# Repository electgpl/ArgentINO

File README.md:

# ArgentINO
Placa de desarrollo basada en Atmega328p compatible con Arduino IDE

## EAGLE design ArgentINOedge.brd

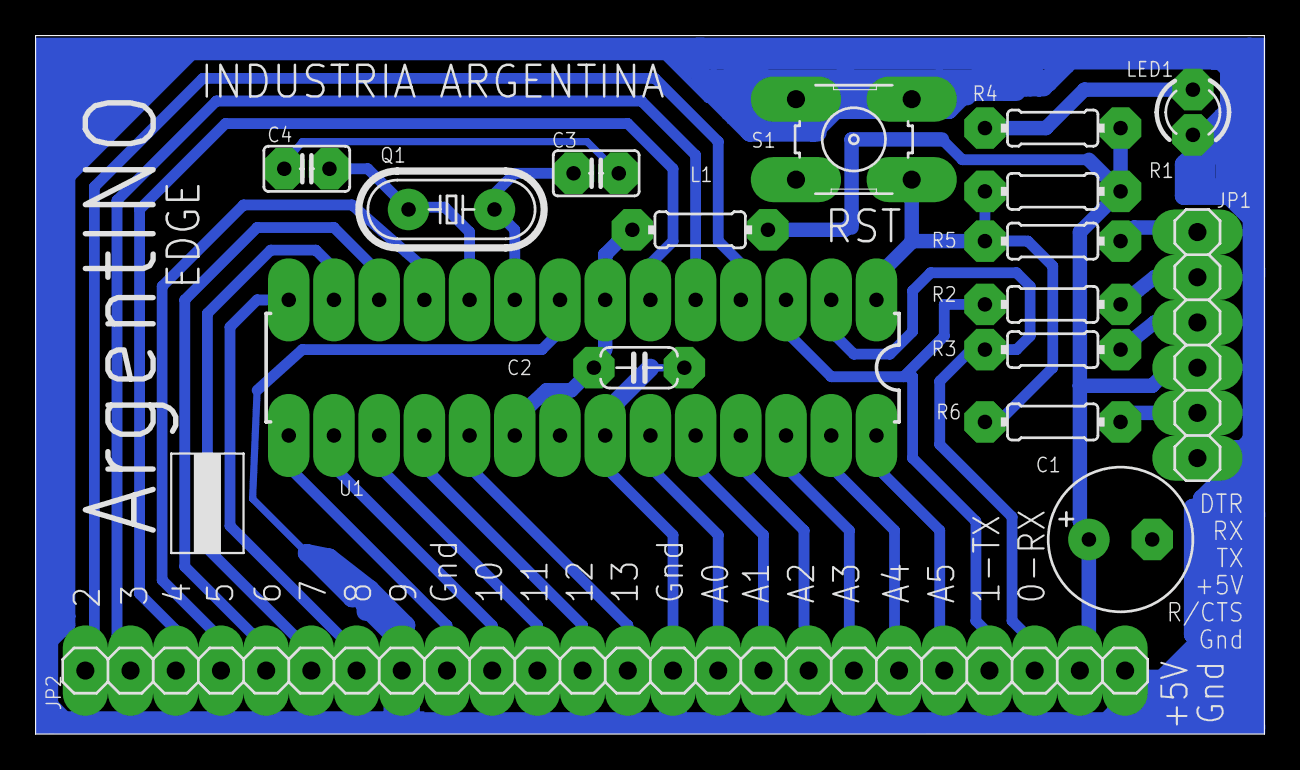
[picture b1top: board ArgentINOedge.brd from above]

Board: 2 copper layers, 69.0 x 39.2 mm, 17 parts (0 on the bottom side), 31 nets.

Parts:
C1: 470uF; E3,5-8
C2: 100nF; C050-024X044
C3, C4: 22pF; C025-025X050
JP1: 1X06
JP2: 1X24
L1: 10uHy; 0204/7
LED1: LED3MM
Q1: 16MHz; HC49/S
R1: 10k; 0204/7
R2, R3, R4: 1k; 0204/7
R5, R6: 100; 0204/7
S1: B3F-10XX
U1: ATMEGA328P_PDIP; DIL28-3

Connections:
0-RX: JP2.3, R3.2, U1.2
1-TX: JP2.4, R2.2, U1.3
2: JP2.24, U1.4
3: JP2.23, U1.5
4: JP2.22, U1.6
5: JP2.21, U1.11
6: JP2.20, U1.12
7: JP2.19, U1.13
8: JP2.18, U1.14
9: JP2.16, U1.15
10: JP2.15, U1.16
11: JP2.14, U1.17
12: JP2.13, U1.18
13: JP2.12, U1.19
+5V: C1.+, JP1.4, JP2.2, L1.1, R1.2, R4.2
A0: JP2.10, U1.23
A1: JP2.9, U1.24
A2: JP2.8, U1.25
A3: JP2.7, U1.26
A4: JP2.6, U1.27
A5: JP2.5, U1.28
DTR: JP1.1, R5.1
unnamed: C3.2, Q1.2, U1.9
unnamed: C4.2, Q1.1, U1.10
unnamed: C2.1, L1.2, U1.7, U1.20
unnamed: C1.-, C2.2, C3.1, C4.1, JP1.6, JP2.1, JP2.11, JP2.17, LED1.K, S1.3, S1.4, U1.8, U1.22
unnamed: LED1.A, R4.1
RST: R1.1, R5.2, R6.2, S1.1, U1.1
RTS: JP1.5, R6.1
RX: JP1.2, R2.1
TX: JP1.3, R3.1

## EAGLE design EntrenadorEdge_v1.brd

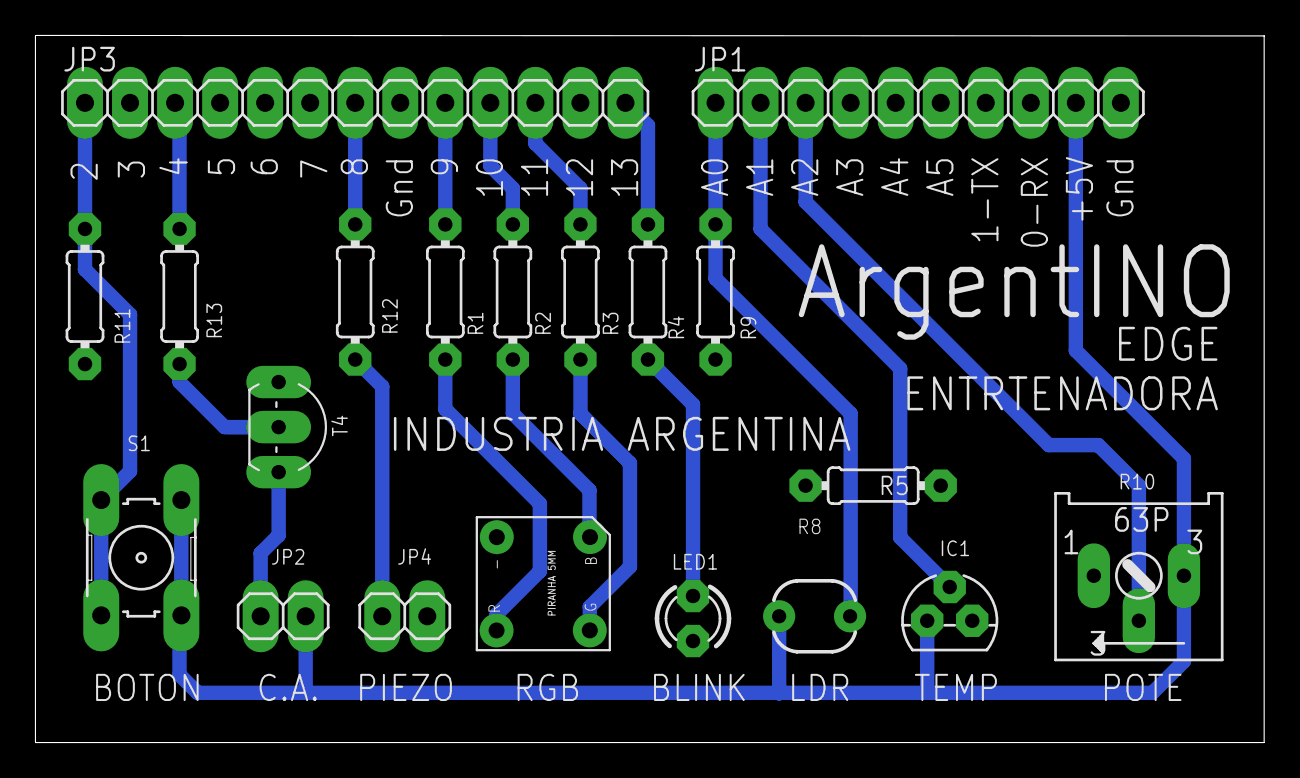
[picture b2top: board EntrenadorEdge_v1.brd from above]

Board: 2 copper layers, 69.3 x 39.9 mm, 20 parts (0 on the bottom side), 19 nets.

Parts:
IC1: LM35CZ; TO92
JP1: 1X10
JP2, JP4: 1X02
JP3: 1X13
LED1: LED3MM
R1, R2, R3: 330; 0204/7
R4, R13: 1k; 0204/7
R5: 0; 0204/7
R8: PHOTOCELLPTH; PHOTOCELL
R9, R11: 10k; 0204/7
R10: S63P
R12: 220; 0204/7
S1: B3F-10XX
T4: 2N3904; TO92-EBC
U$7: LED_PIRANHA_5MM

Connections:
2: JP3.1, R11.2, S1.1, S1.2
4: JP3.3, R13.1
8: JP3.7, R12.1
9: JP3.9, R1.1
10: JP3.10, R2.1
11: JP3.11, R3.1
13: JP3.13, R4.2
+5V: IC1.1, JP1.9, JP2.1, R8.2, R10.E, S1.3, S1.4
A0: JP1.1, R8.1, R9.2
A1: IC1.2, JP1.2
A2: JP1.3, R10.S
unnamed: R2.2, U$7.B
unnamed: R3.2, U$7.G
unnamed: R1.2, U$7.R
unnamed: JP4.2, R12.2
unnamed: R13.2, T4.B
unnamed: JP2.2, T4.C
unnamed: IC1.3, JP1.10, JP3.8, JP4.1, LED1.K, R5.1, R5.2, R9.1, R10.A, R11.1, T4.E, U$7.-
unnamed: LED1.A, R4.1

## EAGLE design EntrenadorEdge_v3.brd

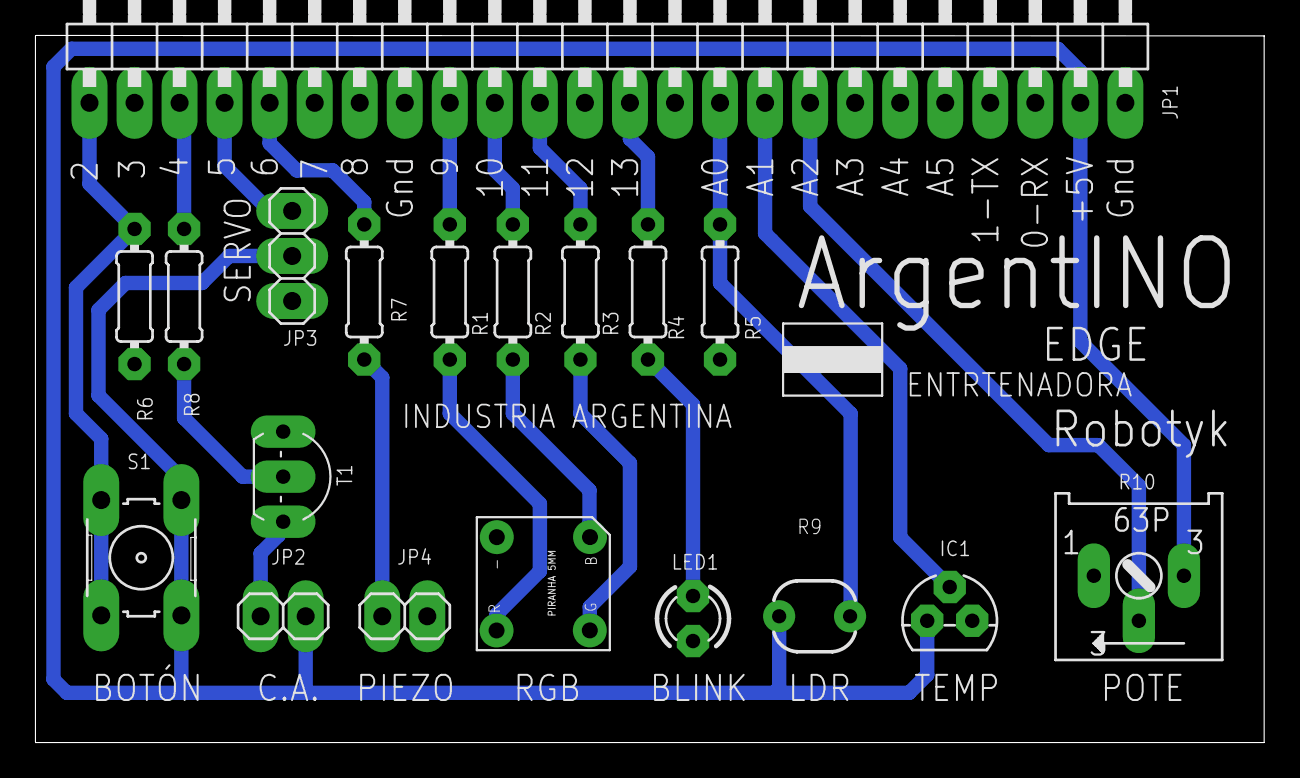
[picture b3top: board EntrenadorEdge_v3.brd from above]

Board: 2 copper layers, 69.3 x 39.9 mm, 19 parts (0 on the bottom side), 20 nets.

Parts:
IC1: LM35CZ; TO92
JP1: 1X24/90
JP2, JP4: 1X02
JP3: 1X03
LED1: LED3MM
R1, R2, R3: 330; 0204/7
R4, R8: 1k; 0204/7
R5, R6: 10k; 0204/7
R7: 220; 0204/7
R9: PHOTOCELLPTH; PHOTOCELL
R10: S63P
S1: B3F-10XX
T1: 2N3904; TO92-EBC
U$7: LED_PIRANHA_5MM

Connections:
2: JP1.1, R6.2, S1.1, S1.2
4: JP1.3, R8.1
5: JP1.4, JP3.3
6: JP1.5, R7.1
9: JP1.9, R1.1
10: JP1.10, R2.1
11: JP1.11, R3.1
13: JP1.13, R4.2
+5V: IC1.1, JP1.23, JP2.1, JP3.2, R9.2, R10.E, S1.3, S1.4
A0: JP1.15, R5.2, R9.1
A1: IC1.2, JP1.16
A2: JP1.17, R10.S
unnamed: R2.2, U$7.B
unnamed: R3.2, U$7.G
unnamed: R1.2, U$7.R
unnamed: JP4.2, R7.2
unnamed: R8.2, T1.B
unnamed: JP2.2, T1.C
unnamed: IC1.3, JP1.8, JP1.14, JP1.24, JP3.1, JP4.1, LED1.K, R5.1, R6.1, R10.A, T1.E, U$7.-
unnamed: LED1.A, R4.1

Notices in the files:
parts and their libraries:
SparkFun-DigitalIC: Licensing: Creative Commons ShareAlike 4.0 International - https://creativecommons.org/licenses/by-sa/4.0
